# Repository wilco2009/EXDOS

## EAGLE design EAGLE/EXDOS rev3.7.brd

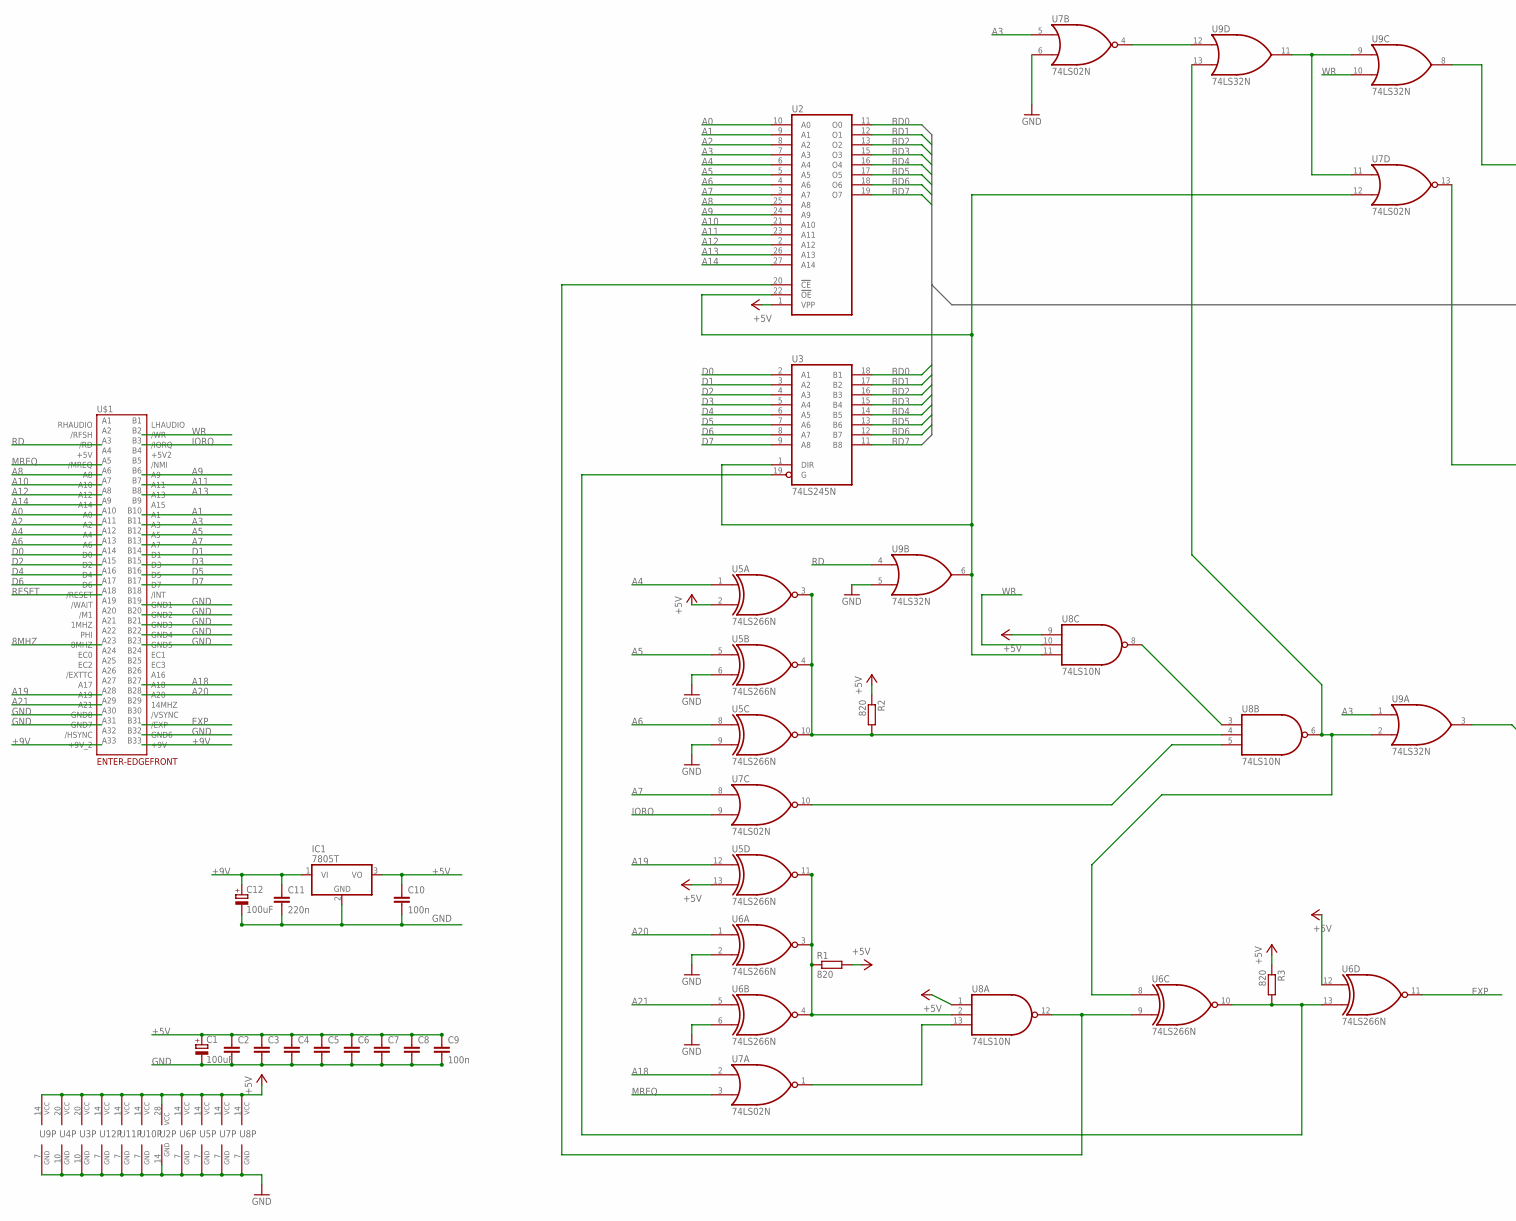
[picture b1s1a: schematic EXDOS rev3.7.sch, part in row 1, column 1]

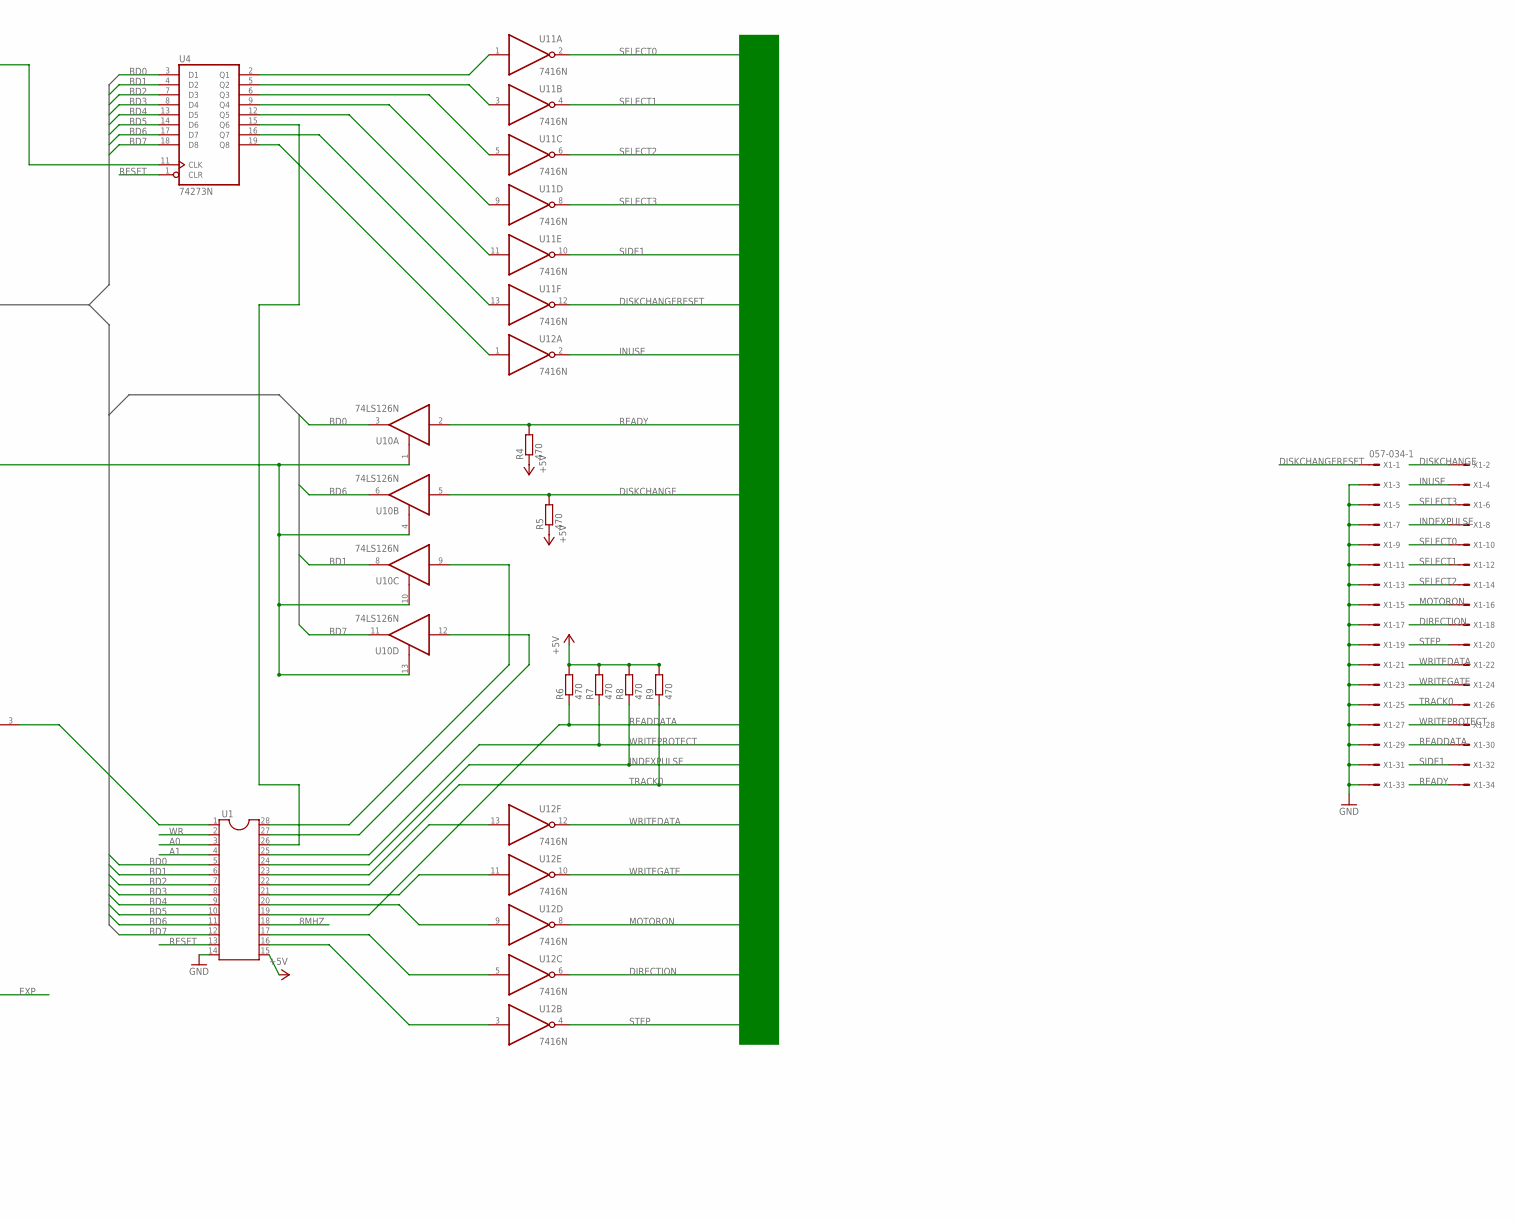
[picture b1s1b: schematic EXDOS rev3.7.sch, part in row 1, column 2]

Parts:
C1, C12: 100uF; E1,8-4
C2, C3, C4, C5, C6, C7, C8: C-EU025-025X050; C025-025X050
C9, C10: 100n; C025-025X050
C11: 220n; C025-025X050
IC1: 7805T; TO220H
R1, R2, R3: 820; 0207/10
R4, R5, R6, R7, R8, R9: 470; 0207/10
U1: DIL28; DIL28-6
U2: 27256; DIL28
U3: 74LS245N; DIL20
U4: 74273N; DIL20
U5, U6: 74LS266N; DIL14
U7: 74LS02N; DIL14
U8: 74LS10N; DIL14
U9: 74LS32N; DIL14
U10: 74LS126N; DIL14
U11, U12: 7416N; DIL14
U$1: ENTER-EDGEFRONT; ENTERPRISE-FRONT
X1: 057-034-1

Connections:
8MHZ: U1.18, U$1.A23 (8MHZ)
+5V: C1.+, C2.1, C3.1, C4.1, C5.1, C6.1, C7.1, C8.1, C9.1, C10.1, IC1.3 (VO), R1.2, R2.1, R3.1, R4.1, R5.1, R6.2, R7.2, R8.2, R9.2, U1.15, U2.1 (VPP), U2.28 (VCC), U3.20 (VCC), U4.20 (VCC), U5.2 (I1), U5.13 (I1), U5.14 (VCC), U6.12 (I0), U6.14 (VCC), U7.14 (VCC), U8.1 (I0), U8.9 (I0), U8.14 (VCC), U9.14 (VCC), U10.14 (VCC), U11.14 (VCC), U12.14 (VCC)
+9V: C11.1, C12.+, IC1.1 (VI), U$1.A33 (+9V_2), U$1.B33 (+9V)
A0: U1.3, U2.10 (A0), U$1.A10 (A0)
A1: U1.4, U2.9 (A1), U$1.B10 (A1)
A2: U2.8 (A2), U$1.A11 (A2)
A3: U2.7 (A3), U7.5 (I0), U9.1 (I0), U$1.B11 (A3)
A4: U2.6 (A4), U5.1 (I0), U$1.A12 (A4)
A5: U2.5 (A5), U5.5 (I0), U$1.B12 (A5)
A6: U2.4 (A6), U5.8 (I0), U$1.A13 (A6)
A7: U2.3 (A7), U7.8 (I0), U$1.B13 (A7)
A8: U2.25 (A8), U$1.A6 (A8)
A9: U2.24 (A9), U$1.B6 (A9)
A10: U2.21 (A10), U$1.A7 (A10)
A11: U2.23 (A11), U$1.B7 (A11)
A12: U2.2 (A12), U$1.A8 (A12)
A13: U2.26 (A13), U$1.B8 (A13)
A14: U2.27 (A14), U$1.A9 (A14)
A18: U7.2 (I0), U$1.B27 (A18)
A19: U5.12 (I0), U$1.A28 (A19)
A20: U6.1 (I0), U$1.B28 (A20)
A21: U6.5 (I0), U$1.A29 (A21)
BD0: U1.5, U2.11 (O0), U3.18 (B1), U4.3 (D1), U10.3 (O)
BD1: U1.6, U2.12 (O1), U3.17 (B2), U4.4 (D2), U10.8 (O)
BD2: U1.7, U2.13 (O2), U3.16 (B3), U4.7 (D3)
BD3: U1.8, U2.15 (O3), U3.15 (B4), U4.8 (D4)
BD4: U1.9, U2.16 (O4), U3.14 (B5), U4.13 (D5)
BD5: U1.10, U2.17 (O5), U3.13 (B6), U4.14 (D6)
BD6: U1.11, U2.18 (O6), U3.12 (B7), U4.17 (D7), U10.6 (O)
BD7: U1.12, U2.19 (O7), U3.11 (B8), U4.18 (D8), U10.11 (O)
D0: U3.2 (A1), U$1.A14 (D0)
D1: U3.3 (A2), U$1.B14 (D1)
D2: U3.4 (A3), U$1.A15 (D2)
D3: U3.5 (A4), U$1.B15 (D3)
D4: U3.6 (A5), U$1.A16 (D4)
D5: U3.7 (A6), U$1.B16 (D5)
D6: U3.8 (A7), U$1.A17 (D6)
D7: U3.9 (A8), U$1.B17 (D7)
DIRECTION: U12.6 (O), X1.18
DISKCHANGE: R5.2, U10.5 (I), X1.2
DISKCHANGERESET: U11.12 (O), X1.1
EXP: U6.11 (O), U$1.B31 (/EXP)
GND: C1.-, C2.2, C3.2, C4.2, C5.2, C6.2, C7.2, C8.2, C9.2, C10.2, C11.2, C12.-, IC1.2 (GND), U1.14, U2.14 (GND), U3.10 (GND), U4.10 (GND), U5.6 (I1), U5.7 (GND), U5.9 (I1), U6.2 (I1), U6.6 (I1), U6.7 (GND), U7.6 (I1), U7.7 (GND), U8.7 (GND), U9.5 (I1), U9.7 (GND), U10.7 (GND), U11.7 (GND), U12.7 (GND), U$1.A30 (GND8), U$1.A31 (GND7), U$1.B19 (GND1), U$1.B20 (GND2), U$1.B21 (GND3), U$1.B22 (GND4), U$1.B23 (GND5), U$1.B32 (GND6), X1.3, X1.5, X1.7, X1.9, X1.11, X1.13, X1.15, X1.17, X1.19, X1.21, X1.23, X1.25, X1.27, X1.29, X1.31, X1.33
INDEXPULSE: R8.1, U1.24, X1.8
INUSE: U12.2 (O), X1.4
IORQ: U7.9 (I1), U$1.B3 (/IORQ)
MOTORON: U12.8 (O), X1.16
MREQ: U7.3 (I1), U$1.A5 (/MREQ)
unnamed: U1.16, U12.3 (I)
unnamed: U1.17, U12.5 (I)
unnamed: R3.2, U3.19 (G), U6.10 (O), U6.13 (I1)
unnamed: R2.2, U5.3 (O), U5.4 (O), U5.10 (O), U8.4 (I1)
unnamed: U7.10 (O), U8.5 (I2)
unnamed: U1.28, U10.9 (I)
unnamed: U1.20, U12.9 (I)
unnamed: U4.2 (Q1), U11.1 (I)
unnamed: U4.5 (Q2), U11.3 (I)
unnamed: U4.6 (Q3), U11.5 (I)
unnamed: U4.9 (Q4), U11.9 (I)
unnamed: U4.12 (Q5), U11.11 (I)
unnamed: U4.16 (Q7), U11.13 (I)
unnamed: U4.19 (Q8), U12.1 (I)
unnamed: U8.3 (I0), U8.8 (O)
unnamed: U1.21, U12.11 (I)
unnamed: R1.1, U5.11 (O), U6.3 (O), U6.4 (O), U8.2 (I1)
unnamed: U2.20 (!CE), U6.9 (I1), U8.12 (O)
unnamed: U7.1 (O), U8.13 (I2)
unnamed: U1.22, U12.13 (I)
unnamed: U7.11 (I0), U9.9 (I0), U9.11 (O)
unnamed: U6.8 (I0), U8.6 (O), U9.2 (I1), U9.13 (I1)
unnamed: U1.1, U9.3 (O)
unnamed: U4.11 (CLK), U9.8 (O)
unnamed: U7.13 (O), U10.1 (OE), U10.4 (OE), U10.10 (OE), U10.13 (OE)
unnamed: U1.27, U10.12 (I)
unnamed: U2.22 (!OE), U3.1 (DIR), U7.12 (I1), U8.11 (I2), U9.6 (O)
unnamed: U7.4 (O), U9.12 (I0)
unnamed: U1.26, U4.15 (Q6)
RD: U9.4 (I0), U$1.A3 (/RD)
READDATA: R6.1, U1.19, X1.30
READY: R4.2, U10.2 (I), X1.34
RESET: U1.13, U4.1 (CLR), U$1.A18 (/RESET)
SELECT0: U11.2 (O), X1.10
SELECT1: U11.4 (O), X1.12
SELECT2: U11.6 (O), X1.14
SELECT3: U11.8 (O), X1.6
SIDE1: U11.10 (O), X1.32
STEP: U12.4 (O), X1.20
TRACK0: R9.1, U1.23, X1.26
WR: U1.2, U8.10 (I1), U9.10 (I1), U$1.B2 (/WR)
WRITEDATA: U12.12 (O), X1.22
WRITEGATE: U12.10 (O), X1.24
WRITEPROTECT: R7.1, U1.25, X1.28

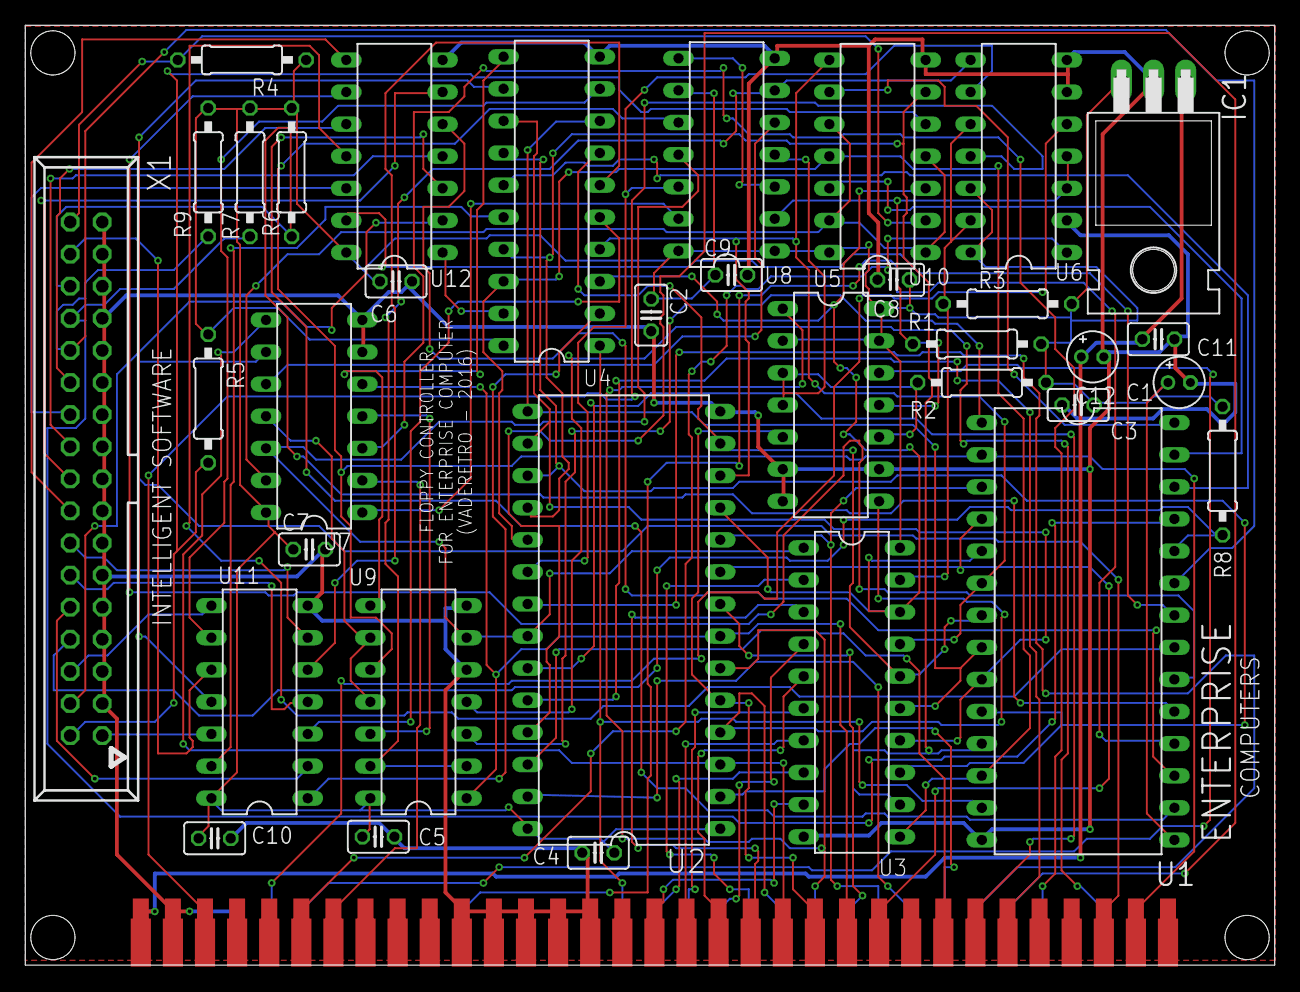
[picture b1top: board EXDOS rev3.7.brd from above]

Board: 4 copper layers, 98.9 x 74.4 mm, 36 parts (0 on the bottom side), 92 nets.
